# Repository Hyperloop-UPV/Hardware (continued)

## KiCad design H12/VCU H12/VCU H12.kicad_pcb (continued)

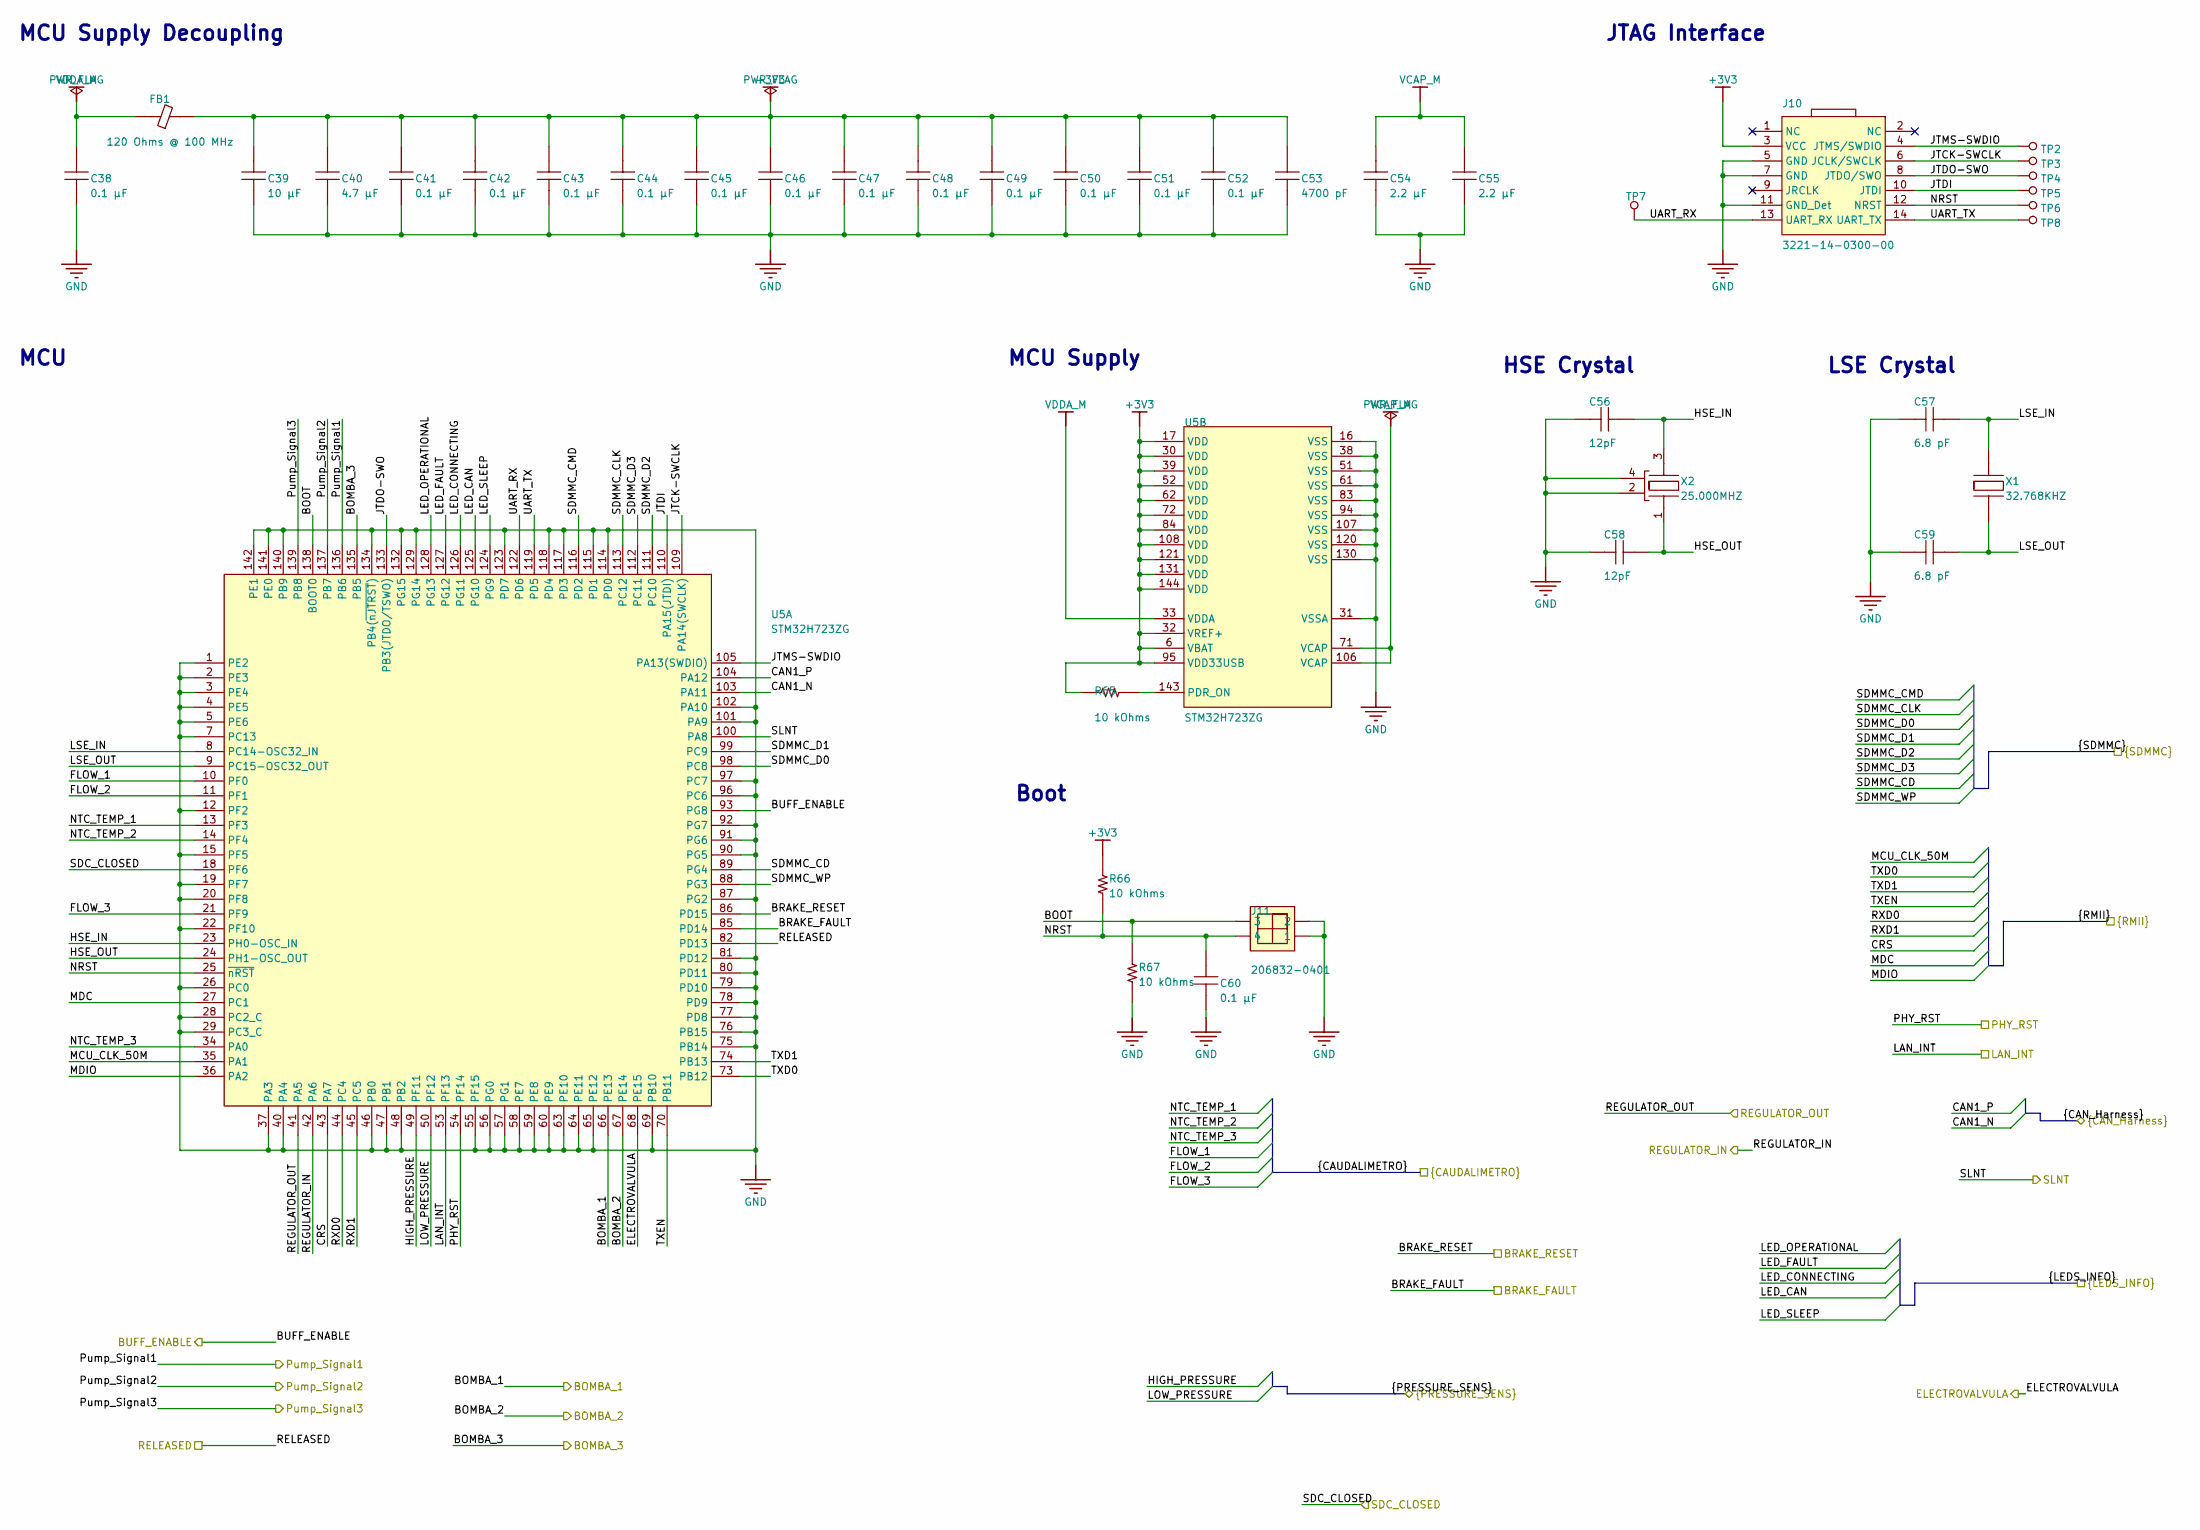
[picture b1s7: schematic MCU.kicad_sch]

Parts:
C38, C41, C42, C43, C44, C45, C46, C47, C48, C49, C50, C51, C52, C60: 0.1 µF; CAP 0603_1608; RATINGS AEC-Q200; TOLERANCE ±10%; PART NUMBER CGA3E2X7R1H104K080AE
C39: 10 µF; CAP 1206_3216 - 0.8MM; TOLERANCE ±10%; VOLTAGE - RATED 50V; PART NUMBER CL31B106KBHNNNE
C40: 4.7 µF; CAP 1206_3216 - 0.8MM; TOLERANCE ±10%; VOLTAGE - RATED 50V; PART NUMBER CL31B475KBHNFNE
C53: 4700 pF; CAP 0603_1608; RATINGS AEC-Q200; TOLERANCE ±10%; PART NUMBER C0603C472K4RECAUTO
C54, C55: 2.2 µF; CAP 1206_3216 - 0.8MM; TOLERANCE ±10%; VOLTAGE - RATED 50V; PART NUMBER CL31B225KBHNFNE
C56, C58: 12pF; CAP 0603_1608; TOLERANCE ±10%; VOLTAGE - RATED 50V; PART NUMBER 06035A120KAT2A
C57, C59: 6.8 pF; CAP 0603_1608; TOLERANCE ±0.25pF; VOLTAGE - RATED 50V; PART NUMBER CC0603CRNPO9BN6R8
FB1: 120 Ohms @ 100 MHz; FER 0805_2012; CURRENT RATING (MAX) 600mA; PART NUMBER BLM21BB121SN1D
J10: 3221-14-0300-00
J11: 206832-0401; 206832-0401-Footprint-1; MAX VOLTAGE 600V AC (RMS)/DC
R65, R66, R67: 10 kOhms; RES 0603_1608; RATINGS AEC-Q200; TOLERANCE ±0.1%; PART NUMBER RNCS0603BKE10K0
TP2, TP3, TP4, TP5, TP6, TP7, TP8: Test point 1.2mm; Test point 1.2mm-Footprint-1
U5: STM32H723ZG; TSQFP50P2200X2200X160-144N
X1: 32.768KHZ; ABS07-120-32.768KHZ-T-Footprint-1
X2: 25.000MHZ; ABM8G-25.000MHZ-18-D2Y-T-Footprint-1

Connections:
+3V3: C39.2, C40.2, C41.2, C42.2, C43.2, C44.2, C45.2, C46.2, C47.2, C48.2, C49.2, C50.2, C51.2, C52.2, C53.2, FB1.2, J10.3 (VCC), R65.2, R66.1, U5.6 (VBAT), U5.17 (VDD), U5.30 (VDD), U5.32 (VREF+), U5.39 (VDD), U5.52 (VDD), U5.62 (VDD), U5.72 (VDD), U5.84 (VDD), U5.95 (VDD33USB), U5.108 (VDD), U5.121 (VDD), U5.131 (VDD), U5.144 (VDD); also elsewhere on the board
/Braking_Sensor/BRAKE_FAULT: U5.85 (PD14); also elsewhere on the board
/Braking_Sensor/BRAKE_RESET: U5.86 (PD15); also elsewhere on the board
/Buffer/BUFF_ENABLE: U5.93 (PG8); also elsewhere on the board
/Buffer/Pump_Signal1: U5.136 (PB6); also elsewhere on the board
/Buffer/Pump_Signal2: U5.137 (PB7); also elsewhere on the board
/Buffer/Pump_Signal3: U5.139 (PB8); also elsewhere on the board
/CAN/CAN1_N: U5.103 (PA11); also elsewhere on the board
/CAN/CAN1_P: U5.104 (PA12); also elsewhere on the board
/Caudalimetro/FLOW_1: U5.10 (PF0); also elsewhere on the board
/Caudalimetro/FLOW_2: U5.11 (PF1); also elsewhere on the board
/Caudalimetro/FLOW_3: U5.21 (PF9); also elsewhere on the board
/Caudalimetro/NTC_TEMP_1: U5.13 (PF3); also elsewhere on the board
/Caudalimetro/NTC_TEMP_2: U5.14 (PF4); also elsewhere on the board
/Caudalimetro/NTC_TEMP_3: U5.34 (PA0); also elsewhere on the board
/Electrovalvula/ELECTROVALVULA: U5.68 (PE15); also elsewhere on the board
/Ethernet_PHY/CRS: U5.43 (PA7); also elsewhere on the board
/Ethernet_PHY/LAN_INT: U5.53 (PF13); also elsewhere on the board
/Ethernet_PHY/MCU_CLK_50M: U5.35 (PA1); also elsewhere on the board
/Ethernet_PHY/MDC: U5.27 (PC1); also elsewhere on the board
/Ethernet_PHY/MDIO: U5.36 (PA2); also elsewhere on the board
/Ethernet_PHY/PHY_RST: U5.54 (PF14); also elsewhere on the board
/Ethernet_PHY/RXD0: U5.44 (PC4); also elsewhere on the board
/Ethernet_PHY/RXD1: U5.45 (PC5); also elsewhere on the board
/Ethernet_PHY/TXD0: U5.73 (PB12); also elsewhere on the board
/Ethernet_PHY/TXD1: U5.74 (PB13); also elsewhere on the board
/Ethernet_PHY/TXEN: U5.70 (PB11); also elsewhere on the board
/Info_LEDs/LED_CAN: U5.125 (PG10); also elsewhere on the board
/Info_LEDs/LED_CONNECTING: U5.126 (PG11); also elsewhere on the board
/Info_LEDs/LED_FAULT: U5.127 (PG12); also elsewhere on the board
/Info_LEDs/LED_OPERATIONAL: U5.128 (PG13); also elsewhere on the board
/Info_LEDs/LED_SLEEP: U5.124 (PG9); also elsewhere on the board
/MCU/BOMBA_1: U5.66 (PE13); also elsewhere on the board
/MCU/BOMBA_2: U5.67 (PE14); also elsewhere on the board
/MCU/BOMBA_3: U5.135 (PB5); also elsewhere on the board
/MCU/BOOT: J11.3, R67.1, U5.138 (BOOT0)
/MCU/HIGH_PRESSURE: U5.49 (PF11); also elsewhere on the board
/MCU/HSE_IN: C56.2, U5.23 (PH0-OSC_IN), X2.3 (XTAL2)
/MCU/HSE_OUT: C58.2, U5.24 (PH1-OSC_OUT), X2.1 (XTAL1)
/MCU/JTCK-SWCLK: J10.6 (JCLK/SWCLK), TP3.1 (*_1), U5.109 (PA14(SWCLK))
/MCU/JTDI: J10.10 (JTDI), TP5.1 (*_1), U5.110 (PA15(JTDI))
/MCU/JTDO-SWO: J10.8 (JTDO/SWO), TP4.1 (*_1), U5.133 (PB3(JTDO/TSWO))
/MCU/JTMS-SWDIO: J10.4 (JTMS/SWDIO), TP2.1 (*_1), U5.105 (PA13(SWDIO))
/MCU/LOW_PRESSURE: U5.50 (PF12); also elsewhere on the board
/MCU/LSE_IN: C57.2, U5.8 (PC14-OSC32_IN), X1.2 (XTAL2)
/MCU/LSE_OUT: C59.2, U5.9 (PC15-OSC32_OUT), X1.1 (XTAL1)
/MCU/NRST: C60.2, J10.12 (NRST), J11.4, R66.2, TP6.1 (*_1), U5.25 (~nRST)
/MCU/REGULATOR_IN: U5.42 (PA6); also elsewhere on the board
/MCU/REGULATOR_OUT: U5.41 (PA5); also elsewhere on the board
/MCU/RELEASED: U5.82 (PD13); also elsewhere on the board
/MCU/SDC_CLOSED: U5.18 (PF6); also elsewhere on the board
/MCU/SDMMC_CD: U5.89 (PG4); also elsewhere on the board
/MCU/SDMMC_CLK: U5.113 (PC12); also elsewhere on the board
/MCU/SDMMC_CMD: U5.116 (PD2); also elsewhere on the board
/MCU/SDMMC_D0: U5.98 (PC8); also elsewhere on the board
/MCU/SDMMC_D1: U5.99 (PC9); also elsewhere on the board
/MCU/SDMMC_D2: U5.111 (PC10); also elsewhere on the board
/MCU/SDMMC_D3: U5.112 (PC11); also elsewhere on the board
/MCU/SDMMC_WP: U5.88 (PG3); also elsewhere on the board
/MCU/SLNT: U5.100 (PA8); also elsewhere on the board
/MCU/UART_RX: J10.13 (UART_RX), TP7.1 (*_1), U5.122 (PD6)
/MCU/UART_TX: J10.14 (UART_TX), TP8.1 (*_1), U5.119 (PD5)
GND: C38.1, C39.1, C40.1, C41.1, C42.1, C43.1, C44.1, C45.1, C46.1, C47.1, C48.1, C49.1, C50.1, C51.1, C52.1, C53.1, C54.1, C55.1, C56.1, C57.1, C58.1, C59.1, C60.1, J10.5 (GND), J10.7 (GND), J10.11 (GND_Det), J11.1, J11.2, R67.2, U5.1 (PE2), U5.2 (PE3), U5.3 (PE4), U5.4 (PE5), U5.5 (PE6), U5.7 (PC13), U5.12 (PF2), U5.15 (PF5), U5.16 (VSS), U5.19 (PF7), U5.20 (PF8), U5.22 (PF10), U5.26 (PC0), U5.28 (PC2_C), U5.29 (PC3_C), U5.31 (VSSA), U5.37 (PA3), U5.38 (VSS), U5.40 (PA4), U5.46 (PB0), U5.47 (PB1), U5.48 (PB2), U5.51 (VSS), U5.55 (PF15), U5.56 (PG0), U5.57 (PG1), U5.58 (PE7), U5.59 (PE8), U5.60 (PE9), U5.61 (VSS), U5.63 (PE10), U5.64 (PE11), U5.65 (PE12), U5.69 (PB10), U5.75 (PB14), U5.76 (PB15), U5.77 (PD8), U5.78 (PD9), U5.79 (PD10), U5.80 (PD11), U5.81 (PD12), U5.83 (VSS), U5.87 (PG2), U5.90 (PG5), U5.91 (PG6), U5.92 (PG7), U5.94 (VSS), U5.96 (PC6), U5.97 (PC7), U5.101 (PA9), U5.102 (PA10), U5.107 (VSS), U5.114 (PD0), U5.115 (PD1), U5.117 (PD3), U5.118 (PD4), U5.120 (VSS), U5.123 (PD7), U5.129 (PG14), U5.130 (VSS), U5.132 (PG15), U5.134 (PB4(~nJTRST)), U5.140 (PB9), U5.141 (PE0), U5.142 (PE1), X2.2 (GND), X2.4 (GND); also elsewhere on the board
unnamed: R65.1, U5.143 (PDR_ON)
VCAP_M: C54.2, C55.2, U5.71 (VCAP), U5.106 (VCAP)
VDDA_M: C38.2, FB1.1, U5.33 (VDDA)

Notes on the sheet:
JTAG Interface
HSE Crystal
LSE Crystal
MCU
Boot
MCU Supply Decoupling
MCU Supply

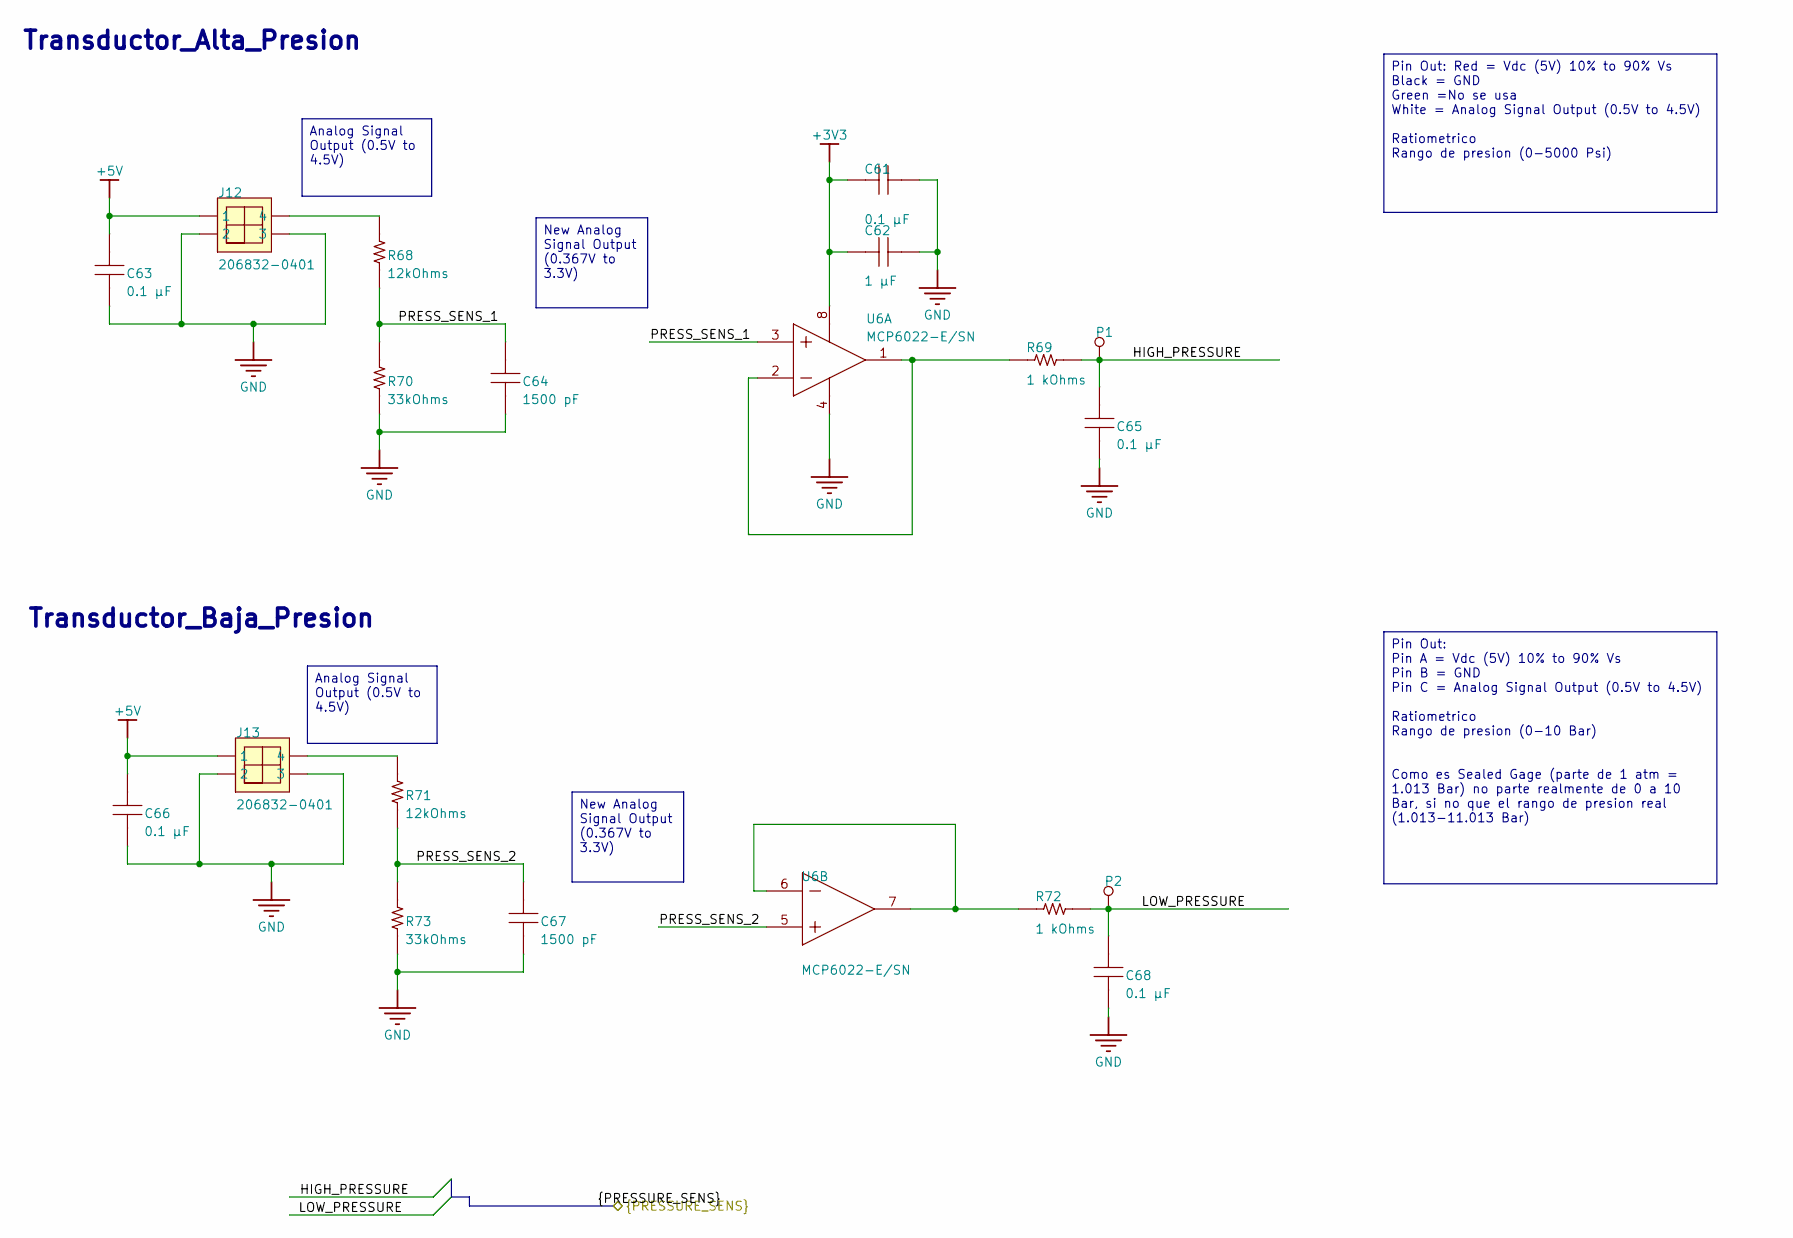
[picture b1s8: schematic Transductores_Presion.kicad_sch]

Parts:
C61, C63, C66: 0.1 µF; CAP 0603_1608; TOLERANCE ±10%; VOLTAGE - RATED 50V; PART NUMBER C0603X104K050T
C62: 1 µF; CAP 1206_3216 - 0.8MM; RATINGS AEC-Q200; TOLERANCE ±10%; PART NUMBER C1206C105K5RACAUTO
C64, C67: 1500 pF; CAP 0603_1608; RATINGS AEC-Q200; TOLERANCE ±10%; PART NUMBER CGA3E2X7R1H152K080AA
C65, C68: 0.1 µF; CAP 0603_1608; RATINGS AEC-Q200; TOLERANCE ±10%; PART NUMBER CGA3E2X7R1H104K080AE
J12, J13: 206832-0401; 206832-0401-Footprint-1; MAX VOLTAGE 600V AC (RMS)/DC
P1, P2: Test point 1.2mm; Test point 1.2mm-Footprint-1
R68, R71: 12kOhms; YAGEO RES 0603_1608; TOLERANCE ±0.1%; PART NUMBER RT0603BRD074K7L
R69, R72: 1 kOhms; YAGEO RES 0603_1608; TOLERANCE ±1%; PART NUMBER RT0603FRE071KL
R70, R73: 33kOhms; YAGEO RES 0603_1608; TOLERANCE ±0.1%; PART NUMBER RT0603BRD079K1L
U6: MCP6022-E/SN; SOIC-SN8_N; VOLTAGE GAIN-MIN 31620; SUPPLY VOLTAGE-NOM (VSU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 5V

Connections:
+3V3: C61.2, C62.1, U6.8 (VDD); also elsewhere on the board
+5V: C63.2, C66.2, J12.1, J13.1; also elsewhere on the board
/MCU/HIGH_PRESSURE: C65.2, P1.1 (*_1), R69.2; also elsewhere on the board
/MCU/LOW_PRESSURE: C68.2, P2.1 (*_1), R72.2; also elsewhere on the board
/Transductores_Presion/PRESS_SENS_1: C64.2, R68.1, R70.2, U6.3 (VINA+)
/Transductores_Presion/PRESS_SENS_2: C67.2, R71.1, R73.2, U6.5 (VINB+)
GND: C61.1, C62.2, C63.1, C64.1, C65.1, C66.1, C67.1, C68.1, J12.2, J12.3, J13.2, J13.3, R70.1, R73.1, U6.4 (VSS); also elsewhere on the board
unnamed: J12.4, R68.2
unnamed: J13.4, R71.2
unnamed: R69.1, U6.1 (VOUTA), U6.2 (VINA-)
unnamed: R72.1, U6.6 (VINB-), U6.7 (VOUTB)

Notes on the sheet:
Transductor_Alta_Presion
Transductor_Baja_Presion
Analog Signal Output (0.5V to 4.5V)
Pin Out: Pin A = Vdc (5V) 10% to 90% Vs Pin B = GND Pin C = Analog Signal Output (0.5V to 4.5V) Ratiometrico Rango de presion (0-10 Bar) Como es Sealed Gage (parte de 1 atm = 1.013 Bar) no parte realmente de 0 a 10 Bar, si no que el rango de presion real (1.013-11.013 Bar)
New Analog Signal Output (0.367V to 3.3V)
Pin Out: Red = Vdc (5V) 10% to 90% Vs Black = GND Green =No se usa White = Analog Signal Output (0.5V to 4.5V) Ratiometrico Rango de presion (0-5000 Psi)

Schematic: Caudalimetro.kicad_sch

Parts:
C69, C74: 0.1 µF; CAP 0603_1608; TOLERANCE ±10%; VOLTAGE - RATED 50V; PART NUMBER C0603X104K050T
C70, C75, C81: 1 µF; CAP 1206_3216 - 0.8MM; RATINGS AEC-Q200; TOLERANCE ±10%; PART NUMBER C1206C105K5RACAUTO
C71, C76, C77: 3300pF; CAP 0603_1608; TOLERANCE ±5%; VOLTAGE - RATED 50V; PART NUMBER 06035C332JAT2A
C72, C73, C78, C79, C80, C82, C83: 0.1 µF; CAP 0603_1608; RATINGS AEC-Q200; TOLERANCE ±10%; PART NUMBER CGA3E2X7R1H104K080AE
IC6: LM339BIPWR; SOP65P640X120-14N; Manufacturer_Part_Number LM339BIPWR; Mouser Part Number 595-LM339BIPWR
J14, J15, J16: 206832-0602
R74, R76, R80, R81, R84, R86: 10 kOhms; RES 0603_1608; TOLERANCE ±0.1%; PART NUMBER MCT06030D1002BP500
R75, R82, R83: 1 kOhms; YAGEO RES 0603_1608; TOLERANCE ±1%; PART NUMBER RT0603FRE071KL
R77, R85, R87, R92: 10 kOhms; RES 0603_1608; RATINGS AEC-Q200; TOLERANCE ±0.1%; PART NUMBER RNCS0603BKE10K0
R78, R88, R89: 47kOhms; YAGEO RES 0603_1608; TOLERANCE ±1%; PART NUMBER RT0603FRE07100KL
R79, R90, R91: 10kOhms; YAGEO RES 0603_1608; RATINGS AEC-Q200; TOLERANCE ±1%; PART NUMBER AC0603FR-07316KL
T1, T2, T3: Test point 1.2mm; Test point 1.2mm-Footprint-1
TP9, TP10, TP11: Test point 1.2mm; Test point 1.2mm-Footprint-1
U7, U8: MCP6022-E/SN; SOIC-SN8_N; VOLTAGE GAIN-MIN 31620; SUPPLY VOLTAGE-NOM (VSU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 5V

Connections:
+3V3: C69.2, C70.1, C74.2, C75.1, J14.4, J15.4, J16.4, R76.2, R77.2, R84.2, R85.2, R86.2, R87.2, U7.8 (VDD), U8.8 (VDD); also elsewhere on the board
+12V: J14.5, J15.5, J16.5, R78.2, R88.2, R89.2; also elsewhere on the board
/Caudalimetro/2.1V_Reference: C73.2, C82.2, C83.2, IC6.6 (1IN-), IC6.8 (3IN-), IC6.10 (4IN-), R78.1, R79.2, R88.1, R89.1, R90.2, R91.2
/Caudalimetro/FLOW_1: IC6.14 (3OUT), R77.1, TP9.1 (*_1); also elsewhere on the board
/Caudalimetro/FLOW_2: IC6.13 (4OUT), R87.1, TP11.1 (*_1); also elsewhere on the board
/Caudalimetro/FLOW_3: IC6.1 (1OUT), R85.1, TP10.1 (*_1); also elsewhere on the board
/Caudalimetro/FLOW_SENS_1: IC6.9 (3IN+), J14.2, R76.1
/Caudalimetro/FLOW_SENS_2: IC6.11 (4IN+), J16.2, R86.1
/Caudalimetro/FLOW_SENS_3: IC6.7 (1IN+), J15.2, R84.1
/Caudalimetro/NTC_TEMP_1: C72.2, R75.2, T1.1 (*_1); also elsewhere on the board
/Caudalimetro/NTC_TEMP_2: C79.2, R83.2, T3.1 (*_1); also elsewhere on the board
/Caudalimetro/NTC_TEMP_3: C78.2, R82.2, T2.1 (*_1); also elsewhere on the board
/Caudalimetro/TEMP_SENS_1: C71.1, J14.3, R74.1, U7.3 (VINA+)
/Caudalimetro/TEMP_SENS_2: C77.1, J16.3, R81.1, U7.5 (VINB+)
/Caudalimetro/TEMP_SENS_3: C76.1, J15.3, R80.1, U8.3 (VINA+)
GND: C69.1, C70.2, C71.2, C72.1, C73.1, C74.1, C75.2, C76.2, C77.2, C78.1, C79.1, C80.1, C81.1, C82.1, C83.1, IC6.12 (GND), J14.1, J14.6, J15.1, J15.6, J16.1, J16.6, R74.2, R79.1, R80.2, R81.2, R90.1, R91.1, R92.1, U7.4 (VSS), U8.4 (VSS); also elsewhere on the board
unnamed: R75.1, U7.1 (VOUTA), U7.2 (VINA-)
unnamed: R83.1, U7.6 (VINB-), U7.7 (VOUTB)
unnamed: R82.1, U8.1 (VOUTA), U8.2 (VINA-)
unnamed: R92.2, U8.5 (VINB+), U8.6 (VINB-)
VBAT: C80.2, C81.2, IC6.3 (VCC); also elsewhere on the board

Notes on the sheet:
Sensor_NTC_1
Caudalimetro_3
FLOW
Sensor_Caudal_1
Caudalimetro_1
Sensor_Caudal_2
Sensor_Caudal_3
Conector_1
Caudalimetro_2
Sensor_NTC_3
NTC
Conector_3
UNUSED CHANNELS
Conector_2
Sensor_NTC_2
Temp Range: -40º to 125º
Como no sabemos si la salida digital del sensor de caudal es open drain o push pull, no nos podemos arriesgar a dañar el micro, por eso usamos este comparador, la idea es cuando se sepa en caso de que sea push pull no soldaremos la pull-up que se encuentra en el pin 5 (entrada positiva) y en caso d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
Adjunto aqui el link de la pagina web, en ella encontramos el datasheet y el manual: https://shop.alphacool.com/en/shop/controllers-and-sensors/flow-sensor/17558-alphacool-es-flow-and-temperature-indicator-highflow-with-rpm-signal Explicando un poco este circuito del caudalimeto tenemos por un lado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

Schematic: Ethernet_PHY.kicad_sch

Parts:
C84, C99: 10 µF; CAP 1206_3216 - 0.8MM; TOLERANCE ±20%; VOLTAGE - RATED 16V; PART NUMBER EMK316BJ106MD-T
C85, C91: 22 µF; CAP 1206_3216 - 0.8MM; TOLERANCE ±10%; VOLTAGE - RATED 16V; PART NUMBER CL31A226KOCLFNC
C86, C87, C88, C89, C90, C92, C93, C94, C97: 0.1 µF; CAP 0603_1608; TOLERANCE ±10%; VOLTAGE - RATED 50V; PART NUMBER C0603C104K5RAC7411
C95, C98: 1 µF; CAP 0603_1608; RATINGS AEC-Q200; TOLERANCE ±10%; PART NUMBER C0603C105K4RACAUTO
C96: 100 pF; CAP 0603_1608; RATINGS AEC-Q200; TOLERANCE ±10%; PART NUMBER C0603C101K5GACAUTO
FB2, FB3, FB4, FB5, FB6, FB7: 120 Ohms @ 100 MHz; FER 0805_2012; CURRENT RATING (MAX) 600mA; PART NUMBER BLM21BB121SN1D
J17: 7499011222A; FLAMMABILITY RATING UL94 V-0
R93, R94, R108, R110, R111, R112: 10 kOhms; RES 0603_1608; RATINGS AEC-Q200; TOLERANCE ±0.1%; PART NUMBER RNCS0603BKE10K0
R95, R96: 330 Ohms; RES 0603_1608; TOLERANCE ±1%; PART NUMBER CRGH0603F330R
R97, R98, R99, R104, R105, R106, R107, R113: 33 Ohms; RES 0603_1608; TOLERANCE ±0.1%; PART NUMBER CPF0603B33RE
R100, R101, R102, R103: 49.9 Ohms; RES 0603_1608; RATINGS AEC-Q200; TOLERANCE ±1%; PART NUMBER RCC060349R9FKEA
R109: 6.49 kOhms; RES 0603_1608; RATINGS AEC-Q200; TOLERANCE ±0.1%; PART NUMBER RQ73C1J6K49BTDF
RV1, RV2, RV3, RV4: 82306050029; WE-VE ULC_0603; WORKING VOLTAGE 5V; CLAMPING VOLTAGE 30V
TP12, TP13, TP14, TP15, TP16, TP17, TP18, TP19, TP20, TP21, TP22, TP23, TP24, TP25, TP26, TP27, TP28, TP29, TP30, TP31, TP32: Test point 1.2mm; Test point 1.2mm-Footprint-1
U9: KSZ8041TLI; FP-TQFP7X7-48LD-PL-1-MFG; SUPPLY VOLTAGE-NOM 3.465V
Y1: 50 MHz; ABRACON ASE; VOLTAGE - SUPPLY 3.3V; PART NUMBER ASE-50.000MHZ-LR-T

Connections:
+3V3: C84.2, C97.2, C98.2, FB2.2, FB6.2, J17.4 (CTD), J17.5 (CRD), R93.2, R95.2, R96.2, R108.2, R110.2, R111.2, Y1.1 (TRI), Y1.4 (VDD); also elsewhere on the board
/Ethernet_PHY/CONFIG0: R93.1, U9.40 (COL/CONFIG0)
/Ethernet_PHY/CRS: R104.2, TP30.1 (*_1); also elsewhere on the board
/Ethernet_PHY/CRS_HF: R104.1, U9.27 (RXDV/CRSDV/CONFIG2)
/Ethernet_PHY/LAN_INT: R111.1, TP25.1 (*_1), U9.32 (INTRP); also elsewhere on the board
/Ethernet_PHY/LED0: J17.10, TP16.1 (*_1), U9.42 (LED0/NWAYEN)
/Ethernet_PHY/LED1: J17.12, TP17.1 (*_1), U9.43 (LED1/SPEED)
/Ethernet_PHY/MCU_CLK_50M: R113.2; also elsewhere on the board
/Ethernet_PHY/MDC: TP31.1 (*_1), U9.19 (MDC); also elsewhere on the board
/Ethernet_PHY/MDIO: R110.1, TP32.1 (*_1), U9.18 (MDIO); also elsewhere on the board
/Ethernet_PHY/PHY_CLK_50M: R107.2, U9.15 (XI/REFCLK/CLOCK)
/Ethernet_PHY/PHY_RST: C99.2, R108.1, TP28.1 (*_1), U9.47 (~RST); also elsewhere on the board
/Ethernet_PHY/REXT: C96.2, R109.2, U9.16 (REXT)
/Ethernet_PHY/RXD0: R94.2, R105.2, TP27.1 (*_1); also elsewhere on the board
/Ethernet_PHY/RXD0_HF: R105.1, U9.23 (RXD0/RXD[0]/RX_DUPLEX)
/Ethernet_PHY/RXD1: R106.2, TP29.1 (*_1); also elsewhere on the board
/Ethernet_PHY/RXD1_HF: R106.1, U9.22 (RXD1/RXD[1]/PHYAD2)
/Ethernet_PHY/RXER: R112.2, U9.29 (RXER/RX_ER/ISO)
/Ethernet_PHY/RX_N: J17.6 (RD-), R102.2, RV4.1, TP21.1 (*_1), U9.9 (RX-)
/Ethernet_PHY/RX_P: J17.3 (RD+), R103.2, RV3.1, TP20.1 (*_1), U9.10 (RX+)
/Ethernet_PHY/TXD0: R98.1, TP23.1 (*_1); also elsewhere on the board
/Ethernet_PHY/TXD0_HF: R98.2, U9.35 (TXD0/TXD[0]/TX)
/Ethernet_PHY/TXD1: R99.1, TP24.1 (*_1); also elsewhere on the board
/Ethernet_PHY/TXD1_HF: R99.2, U9.36 (TXD1/TXD[1]/SYNC)
/Ethernet_PHY/TXEN: R97.1, TP26.1 (*_1); also elsewhere on the board
/Ethernet_PHY/TXEN_HF: R97.2, U9.34 (TXEN/TX_EN)
/Ethernet_PHY/TX_N: J17.2 (TD-), R100.2, RV2.1, TP19.1 (*_1), U9.11 (TX-)
/Ethernet_PHY/TX_P: J17.1 (TD+), R101.2, RV1.1, TP18.1 (*_1), U9.12 (TX+)
ETH_Shield: FB4.1, J17.Shell (Shield), RV1.2, RV2.2, RV3.2, RV4.2
GND: C84.1, C85.1, C86.1, C87.1, C88.1, C89.1, C90.1, C91.1, C92.1, C93.1, C94.1, C95.1, C96.1, C97.1, C98.1, C99.1, FB5.2, J17.8 (GND), R94.1, R109.1, R112.1, U9.1 (GND), U9.2 (GND), U9.3 (GND), U9.13 (GND), U9.17 (GND), U9.24 (GND), U9.30 (GND), U9.33 (TXC), U9.37 (GND), U9.38 (TXD2), U9.39 (TXD3), U9.41 (CRS/CONFIG1), Y1.2 (GND); also elsewhere on the board
unnamed: C89.2, R100.1, R101.1
unnamed: C90.2, R102.1, R103.1
unnamed: FB4.2, FB5.1
unnamed: J17.9, R95.1
unnamed: J17.11, R96.1
unnamed: R107.1, R113.1, Y1.3 (OUT)
V1.8_OUT: C94.2, C95.2, FB3.2, FB7.2, TP22.1 (*_1), U9.6 (V1.8_OUT)
VDDA_1.8: C87.2, C88.2, FB3.1, TP13.1 (*_1), U9.4 (VDDA_1.8), U9.5 (VDDA_1.8)
VDDA_3.3: C91.2, C92.2, FB6.1, TP14.1 (*_1), U9.7 (VDDA_3.3), U9.8 (VDDA_3.3)
VDDIO_3.3: C85.2, C86.2, FB2.1, TP15.1 (*_1), U9.25 (VDDIO_3.3), U9.26 (VDDIO_3.3)
VDD_1.8: C93.2, FB7.1, TP12.1 (*_1), U9.31 (VDD_1.8)

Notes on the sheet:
ESD Protection
Strap-In Options
Biasing
Layout Notes
50 MHz Clock
Analog Interface
Transceiver Supply Decoupling
Slew Rate Control
Reset
Ethernet Transceiver
Default Strap-ins: PHY Adress = 00001 Isolate Mode = Disable Speed = 100 Mbps Auto-Negotiation = Enable Interface = RMII
Place these sereis resistors close to the MCU
Place these series resistors close to the PHY
Route analog RX (RX_P, RX_N) and TX (TX_P, TX_N) pairs as differential signals with a 100 Ohm impedance profile, in a coplanar differential microstrip or stripline configuration. The calculations for trace width have been made according to the manufacturing specs listed in the main architecture she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
Keep all RMII traces below 150mm. Avoid using vias on RMII signals, if necessary, use the same number of vias for all signals. Length match the following signals to <5 mm: TXD0, TXD1, TXEN, length matched to each other (RMII_TX net class). RXD0, RXD1, CRS, length matched to each other (RMII_RX net 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
All RMII signals need to be routed using a 50 Ohm coplanar microstrip or stripline impedance profile: The calculations for trace width have been made according to the manufacturing specs listed in the main architecture sheet of this PCB and assuming a coplanar routing approach (0.1mm clearance to G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
Create a ground plane beneath the ethernet connector with the ETH_Shield net. Terminate ESD protection diodes to ETH_Shield plane. Bond ETH_Shield to GND using ferrite beads at a single bonding point.
Pulldown = Full-Duplex NC = Half-Duplex
Pullup = RMII Interface NC = MII Interface

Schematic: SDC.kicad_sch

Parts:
C100: 0.1 µF; CAP 0603_1608; RATINGS AEC-Q200; TOLERANCE ±10%; PART NUMBER CGA3E2X7R1H104K080AE
IC6: LM339BIPWR; SOP65P640X120-14N; Manufacturer_Part_Number LM339BIPWR; Mouser Part Number 595-LM339BIPWR
J18: 216571-2002; 216571-2002-Footprint-1
R114, R116: 10 kOhms; RES 0603_1608; RATINGS AEC-Q200; TOLERANCE ±0.1%; PART NUMBER RNCS0603BKE10K0
R115: 100 kOhms; YAGEO RES 0603_1608; TOLERANCE ±1%; PART NUMBER RT0603FRE07100KL
R117: 270 kOhms; YAGEO RES 0603_1608; RATINGS AEC-Q200; TOLERANCE ±1%; PART NUMBER AC0603FR-07316KL
TP33: Test point 1.2mm; Test point 1.2mm-Footprint-1

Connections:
+3V3: R114.2; also elsewhere on the board
+24_SDC: IC6.5 (2IN+), J18.1, J18.2, R116.2; also elsewhere on the board
/MCU/SDC_CLOSED: IC6.2 (2OUT), R114.1, TP33.1 (*_1); also elsewhere on the board
/SDC/18V_Reference: C100.2, IC6.4 (2IN-), R115.1, R117.2
GND: C100.1, R116.1, R117.1; also elsewhere on the board
VBAT: R115.2; also elsewhere on the board

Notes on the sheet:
SDC Input & Measurement
Output is open drain. Intentionally no hysteresis
Low = SDC Open

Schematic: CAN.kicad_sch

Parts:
C101, C103: 47 pF; CAP 0603_1608; TOLERANCE ±5%; VOLTAGE - RATED 50V; PART NUMBER 885012006055
C102: 4700pF; CAP 0603_1608; TOLERANCE ±5%; VOLTAGE - RATED 50V; PART NUMBER 06035C472JAT2A
C104, C105: 0.1 µF; CAP 0603_1608; TOLERANCE ±10%; VOLTAGE - RATED 50V; PART NUMBER C0603C104K5RAC7411
D29: PESD1CAN,215; PESD1CAN,215-Footprint-1
J19, J20: 22-28-4020; 22-28-4020-Footprint-1; MAXIMUM VOLTAGE 250 V
J21, J22: 206832-0401; 206832-0401-Footprint-1; MAX VOLTAGE 600V AC (RMS)/DC
L3: DLW43SH510XK2L; FP-DLW43-0_2-t2_6-e0_7-MFG; CURRENT RATING 230mA; VOLTAGE RATING 50V
R118, R122: 62 Ohms; RES 0603_1608; RATINGS AEC-Q200; TOLERANCE ±0.1%; PART NUMBER RNCS0603BKE10K0
R119, R120, R121: 100 Ohms; RES 0603_1608; TOLERANCE ±1%; PART NUMBER CRCW0603100RFKEAC
RX1: Test point 1.2mm; Test point 1.2mm-Footprint-1
TX1: Test point 1.2mm; Test point 1.2mm-Footprint-1
U10: TJA1051T/3,118; NXP-SOIC-8_N

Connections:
+3V3: C104.2, U10.5 (VIO); also elsewhere on the board
+5V: C105.2, U10.3 (VCC); also elsewhere on the board
/CAN/CAN1_N: R120.1, RX1.1 (*_1); also elsewhere on the board
/CAN/CAN1_P: R119.1, TX1.1 (*_1); also elsewhere on the board
/CAN/CANT_N: L3.4, R122.2, U10.6 (CANL)
/CAN/CANT_P: L3.1, R118.1, U10.7 (CANH)
/CAN/CAN_N: C103.1, D29.1, J21.4, J22.4, L3.3
/CAN/CAN_P: C101.2, D29.2, J21.3, J22.3, L3.2
/MCU/SLNT: R121.2; also elsewhere on the board
GND: C101.1, C102.1, C103.2, C104.1, C105.1, D29.3, J21.2, J22.2, U10.2 (GND); also elsewhere on the board
unnamed: C102.2, J19.1
unnamed: J19.2, J20.2, R118.2
unnamed: J20.1, R122.1
unnamed: R120.2, U10.4 (RXD)
unnamed: R121.1, U10.8 (S)
unnamed: R119.2, U10.1 (TXD)
VBAT: J21.1, J22.1; also elsewhere on the board

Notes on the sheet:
CAN Connector
CAN
HIGH = Silent Mode LOW = Normal Mode
Place decoupling capacitors closed to supply pins

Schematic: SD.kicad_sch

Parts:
C106: 10 µF; CAP 1206_3216 - 0.8MM; TOLERANCE ±10%; VOLTAGE - RATED 50V; PART NUMBER CL31B106KBHNNNE
C107: 0.1 µF; CAP 0603_1608; RATINGS AEC-Q200; TOLERANCE ±10%; PART NUMBER CGA3E2X7R1H104K080AE
FB8, FB9: 120 Ohms @ 100 MHz; FER 0805_2012; CURRENT RATING (MAX) 600mA; PART NUMBER BLM21BB121SN1D
J23: 1939115-1; TE_1939115-1
R123, R124, R125, R126, R127, R128, R129: 10 kOhms; RES 0603_1608; RATINGS AEC-Q200; TOLERANCE ±0.1%; PART NUMBER RNCS0603BKE10K0
R130, R131, R132, R133, R134, R135, R136, R137: 33 Ohms; RES 0603_1608; TOLERANCE ±0.1%; PART NUMBER CPF0603B33RE
RV5, RV6, RV7, RV8, RV9, RV10, RV11, RV12: 82306050029; WE-VE ULC_0603; WORKING VOLTAGE 5V; CLAMPING VOLTAGE 30V
TP34, TP35, TP36, TP37, TP38, TP39, TP40, TP41: Test point 1.2mm; Test point 1.2mm-Footprint-1

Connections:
+3V3: C106.2, C107.2, J23.4, R123.2, R124.2, R125.2, R126.2, R127.2, R128.2, R129.2; also elsewhere on the board
/MCU/SDMMC_CD: R136.1; also elsewhere on the board
/MCU/SDMMC_CLK: R131.1; also elsewhere on the board
/MCU/SDMMC_CMD: R130.1; also elsewhere on the board
/MCU/SDMMC_D0: R132.1; also elsewhere on the board
/MCU/SDMMC_D1: R133.1; also elsewhere on the board
/MCU/SDMMC_D2: R134.1; also elsewhere on the board
/MCU/SDMMC_D3: R135.1; also elsewhere on the board
/MCU/SDMMC_WP: R137.1; also elsewhere on the board
/SD/SDMMC_CD_HF: J23.10 (CD), R128.1, R136.2, RV12.1, TP40.1 (*_1)
/SD/SDMMC_CLK_HF: J23.5, R131.2, RV7.1, TP35.1 (*_1)
/SD/SDMMC_CMD_HF: J23.2, R123.1, R130.2, RV8.1, TP34.1 (*_1)
/SD/SDMMC_D0_HF: J23.7, R124.1, R132.2, RV10.1, TP36.1 (*_1)
/SD/SDMMC_D1_HF: J23.8, R125.1, R133.2, RV9.1, TP37.1 (*_1)
/SD/SDMMC_D2_HF: J23.9, R126.1, R134.2, RV6.1, TP38.1 (*_1)
/SD/SDMMC_D3_HF: J23.1, R127.1, R135.2, RV5.1, TP39.1 (*_1)
/SD/SDMMC_WP_HF: J23.12 (WP), R129.1, R137.2, RV11.1, TP41.1 (*_1)
GND: C106.1, C107.1, FB9.2, J23.3, J23.6, J23.11 (COMM); also elsewhere on the board
unnamed: FB8.2, FB9.1
SD_Shield: FB8.1, J23.SH1 (SHIELD), J23.SH2 (SHIELD), RV5.2, RV6.2, RV7.2, RV8.2, RV9.2, RV10.2, RV11.2, RV12.2

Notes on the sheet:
ESD Protection
Slew Rate Control
Layout Notes
SD Card Slot
Pull-Up
The followoing signals need to be routed using a 50 Ohm coplanar microstrip or stripline impedance profile: CMD, CLK, D0, D1, D2, D3. The calculations for trace width have been made according to the manufacturing specs listed in the main architecture sheet of this PCB and assuming a coplanar routin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
Keep SDMMC traces below 120mm. Avoid using vias on SDMMC signals, if necessary, use the same number of vias for all signals. Length match the following signals to <10 mm: CMD, CLK, D0, D1, D2, D3, length matched to each other (SDMMC net class).
Create a ground plane beneath the SD card connector with the SD_Shield net. Terminate ESD protection diodes to SD_Shield plane. Bond SD_Shield to GND using ferrite beads at a single bonding point.
Place these series resitors close to the MCU.
Place these pullup resistors close to the MCU.
CD (Card-Detect) and WP (Write-Protect) switch handling: Either use pull-ups and connect to MCU, or hard-tie to GND when not used, preserving MCU pins.

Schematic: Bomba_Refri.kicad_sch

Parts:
D30, D32, D34: Green; LED 0603_1608 GREEN; MILLICANDELA RATING 15mcd; VOLTAGE - FORWARD (VF) 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 2.1V; PART NUMBER QTLP601C4TR
D31, D33, D35: RS1B-13-F; DO214AC SMA; VOLTAGE - DC REVERSE (V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 100 V; VOLTAGE - FORWARD (VF) 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 1.3 V @ 1 A; PART NUMBER RS1B-13-F
J24, J25, J26: 206832-0401; 206832-0401-Footprint-1; MAX VOLTAGE 600V AC (RMS)/DC
Q2, Q3, Q6: AO4407A; Manufacturer_Part_Number AO4407A
Q4, Q5, Q7: MMBT3904; SOT95P230X110-3N; Manufacturer_Part_Number MMBT3904
R138, R139, R140, R141, R146, R147: 1k; RES 0603_1608
R142, R143, R148: 10kOhms; RES 0603_1608; RATINGS AEC-Q200; TOLERANCE ±1%; PART NUMBER CRGCQ0603F330R
R144, R145, R149: 1.5 kOhms; RES 0603_1608; RATINGS AEC-Q200; TOLERANCE ±0.1%; PART NUMBER RNCS0603BKE10K0

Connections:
+12V: Q2.1 (S_1), Q2.2 (S_2), Q2.3 (S_3), Q3.1 (S_1), Q3.2 (S_2), Q3.3 (S_3), Q6.1 (S_1), Q6.2 (S_2), Q6.3 (S_3), R138.1, R139.1, R146.1; also elsewhere on the board
/Buffer/Pump_Signal1CN: J24.3; also elsewhere on the board
/Buffer/Pump_Signal2CN: J25.3; also elsewhere on the board
/Buffer/Pump_Signal3CN: J26.3; also elsewhere on the board
/MCU/BOMBA_1: R140.1, R142.2; also elsewhere on the board
/MCU/BOMBA_2: R141.1, R143.2; also elsewhere on the board
/MCU/BOMBA_3: R147.1, R148.2; also elsewhere on the board
GND: D30.2, D31.1, D32.2, D33.1, D34.2, D35.1, J24.2, J25.2, J26.2, Q4.2 (E), Q5.2 (E), Q7.2 (E), R142.1, R143.1, R148.1; also elsewhere on the board
unnamed: D30.1, R144.1
unnamed: D32.1, R145.1
unnamed: D34.1, R149.1
unnamed: D31.2, J24.1, J24.4, Q2.5 (D_1), Q2.6 (D_2), Q2.7 (D_3), Q2.8 (D_4), R144.2
unnamed: Q2.4 (G), Q4.3 (C), R138.2
unnamed: D33.2, J25.1, J25.4, Q3.5 (D_1), Q3.6 (D_2), Q3.7 (D_3), Q3.8 (D_4), R145.2
unnamed: Q3.4 (G), Q5.3 (C), R139.2
unnamed: Q4.1 (B), R140.2
unnamed: Q5.1 (B), R141.2
unnamed: D35.2, J26.1, J26.4, Q6.5 (D_1), Q6.6 (D_2), Q6.7 (D_3), Q6.8 (D_4), R149.2
unnamed: Q6.4 (G), Q7.3 (C), R146.2
unnamed: Q7.1 (B), R147.2

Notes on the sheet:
BOMBA_2
BOMBA_1
BOMBA_3
Encedemos bomba con nivel alto 3.3V
se pueden mirar otros mosfets para simplificar
